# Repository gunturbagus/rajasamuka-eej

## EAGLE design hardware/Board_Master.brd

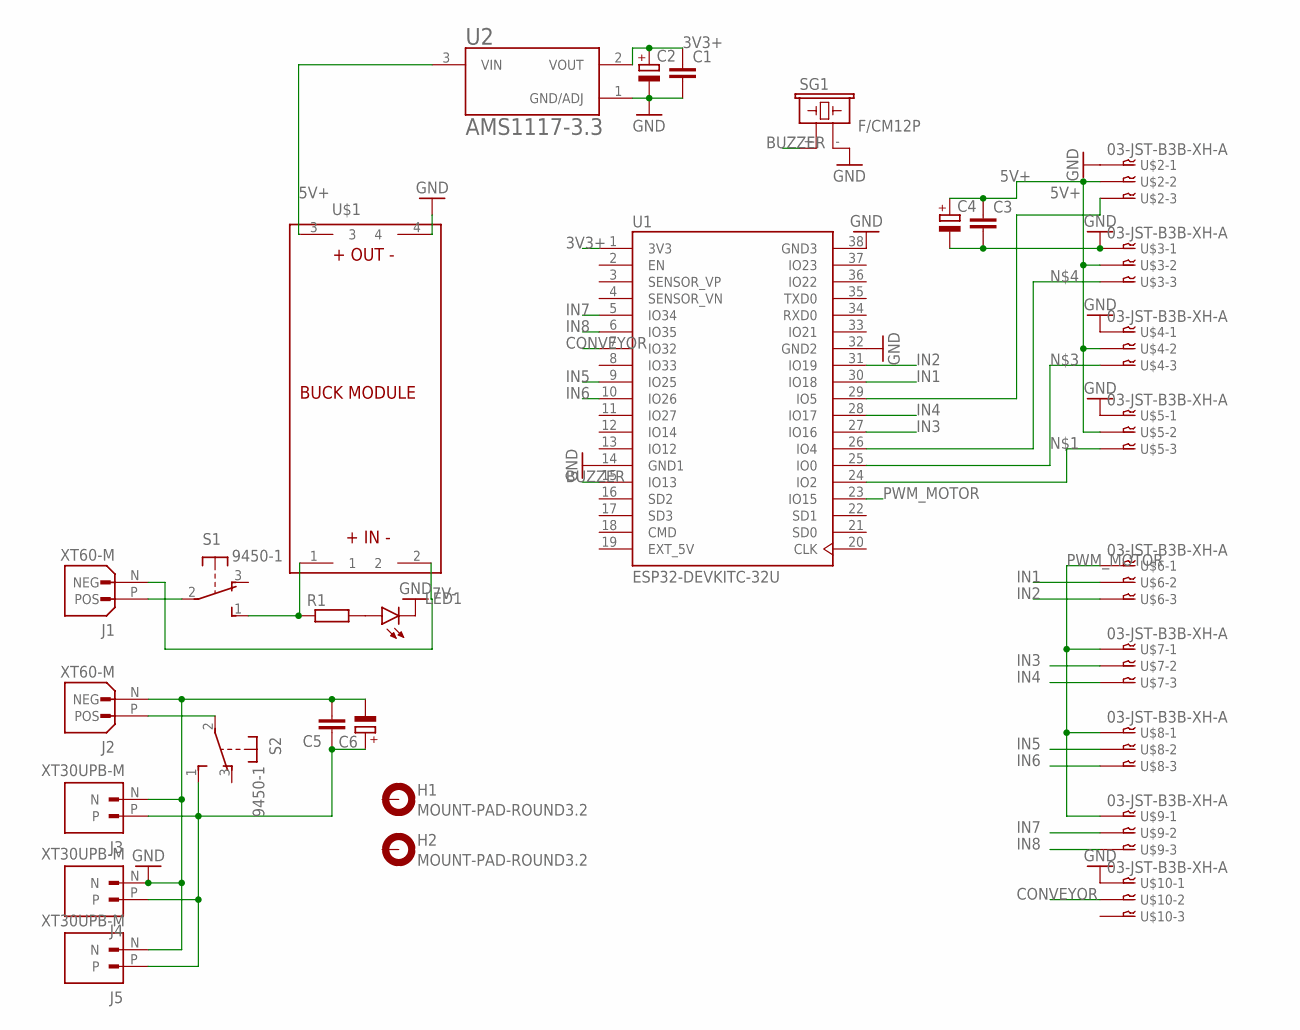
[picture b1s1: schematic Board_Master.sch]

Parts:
C1, C3, C5: C-EU025-030X050; C025-030X050
C2, C4, C6: CPOL-EUE2.5-7; E2,5-7
H1, H2: MOUNT-PAD-ROUND3.2; 3,2-PAD
J1, J2: XT60-M; AMASS_XT60-M
J3, J4, J5: XT30UPB-M; AMASS_XT30UPB-M
LED1: LED5MM
R1: R-EU_0207/10; 0207/10
S1, S2: 9450-1
SG1: F/CM12P
U1: ESP32-DEVKITC-32U; MODULE_ESP32-DEVKITC-32U
U2: AMS1117-3.3; SOT229P700X180-4N
U$1: BUCK_MODULEWITH_SMDPADS&THROUGHHOLES; BUCK_MODULE
U$2, U$3, U$4, U$5, U$6, U$7, U$8, U$9, U$10: 03-JST-B3B-XH-A; B3B-XH

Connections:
3V3+: C1.1, C2.+, U1.1 (3V3), U2.2 (VOUT)
5V+: C3.1, C4.+, U2.3 (VIN), U$1.3, U$2.P$2, U$3.P$2, U$4.P$2, U$5.P$2
7V-: J1.N (NEG), U$1.2
BUZZER: SG1.+ (1), U1.15 (IO13)
CONVEYOR: U1.7 (IO32), U$10.P$2
EXT_5V: U1.19 (EXT_5V)
GND: C1.2, C2.-, C3.2, C4.-, C5.2, C6.-, J2.N (NEG), J3.N, J4.N, J5.N, LED1.K (C), SG1.- (2), U1.14 (GND1), U1.32 (GND2), U1.38 (GND3), U2.1 (GND/ADJ), U$1.4, U$2.P$1, U$3.P$1, U$4.P$1, U$5.P$1, U$10.P$1
IN1: U1.30 (IO18), U$6.P$2
IN2: U1.31 (IO19), U$6.P$3
IN3: U1.27 (IO16), U$7.P$2
IN4: U1.28 (IO17), U$7.P$3
IN5: U1.9 (IO25), U$8.P$2
IN6: U1.10 (IO26), U$8.P$3
IN7: U1.5 (IO34), U$9.P$2
IN8: U1.6 (IO35), U$9.P$3
unnamed: U1.24 (IO2), U$5.P$3
unnamed: U1.29 (IO5), U$2.P$3
unnamed: U1.25 (IO0), U$4.P$3
unnamed: U1.26 (IO4), U$3.P$3
unnamed: J2.P (POS), S2.2
unnamed: J1.P (POS), S1.2
unnamed: C5.1, C6.+, J3.P, J4.P, J5.P, S2.1 (S)
unnamed: R1.1, S1.1 (S), U$1.1
unnamed: LED1.A, R1.2
PWM_MOTOR: U1.23 (IO15), U$6.P$1, U$7.P$1, U$8.P$1, U$9.P$1

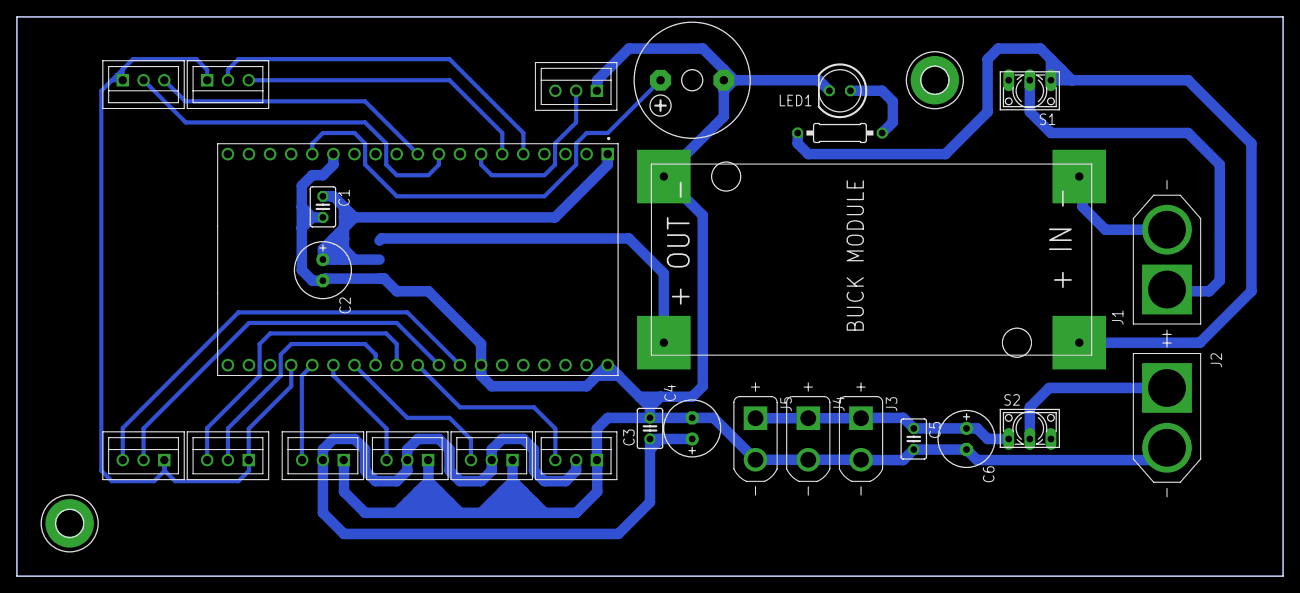
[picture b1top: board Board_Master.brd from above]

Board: 2 copper layers, 152.4 x 67.3 mm, 30 parts (1 on the bottom side), 24 nets.

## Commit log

2025-11-08 final
